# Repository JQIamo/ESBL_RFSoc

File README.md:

# ESBL_RFSoc

Pure sinusoidal phase modulator for electronic sideband locking (ESB locking/ESBL) based on the [RFSoC 4x2](https://www.realdigital.org/hardware/rfsoc-4x2) platform.

## Table of Contents

- [Overview](#overview)
- [Project Structure](#project-structure)
- [System Architecture](#system-architecture)
- [Operation Theory](#operation-theory)
- [Paper and Contact](#paper-and-contact)

## Overview

This repository contains the hardware and software for an RFSoC-based direct SDR that generates the phase-modulated radio-frequency (rf) drive used in electronic sideband Pound–Drever–Hall (PDH) laser locking. The design runs on the AMD Zynq UltraScale+ RFSoC ZU48DR on the [RFSoC 4x2](https://www.realdigital.org/hardware/rfsoc-4x2) platform. It synthesizes the required in-phase and quadrature-phase (I/Q) baseband waveforms in the programmable logic (PL), then uses the on-chip RF Data Converter (RFDC) and RF digital-to-analog converter (RF-DAC) to produce the analog output for an electro-optic modulator (EOM).

The repository includes the FPGA gateware and its Migen source, the PYNQ-side control server and startup scripts, and host-side integration with labscript/BLACS. It also contains the KiCad design for an RFSoC adapter board, simulation testbenches, and Jupyter notebooks for hardware tests. The interface software controls the modulation frequency and depth, I/Q amplitudes and relative phase, PDH reference phase, DAC carrier frequency and output level, and programmed carrier-frequency ramps.

## Project Structure

The main directories and their roles are:

```text
.
├── PYNQ_interface/
│   ├── parser.py
│   ├── ESBL_autostart.sh
│   ├── ESBL_service_enable.sh
│   └── ESBL_startup.service
├── gateware/
│   ├── hdl/
│   ├── python/
│   ├── scripts/
│   ├── sim/
│   └── makefile
├── kicad/
│   └── esb_rfsoc_adapter/
├── labscript_devices/
│   └── ESBL_RFSoC/
└── notebooks/
```

- **`PYNQ_interface/`** — Runtime software for the RFSoC processing system (PS). `parser.py` loads the FPGA overlay, configures the RFDC and memory-mapped control registers, and runs the TCP/IP command server. The shell scripts and systemd unit install and launch the server automatically at boot. The accompanying directory README describes deployment on the board.

- **`gateware/hdl/`** — Verilog RTL used by the Vivado design. The main modules implement the phase-modulated I/Q waveform generator, AXI-Lite control registers, the DMA-driven RFDC NCO frequency-update controller, trigger logic, and the serialized reference output. The `.init` files provide lookup-table initialization data used by the waveform generator. The directory also includes the board-level top-level and wrapper HDL files.

- **`gateware/python/`** — Migen source used to generate the phase-generator Verilog. `esbl_parallel_with_PDH.py` generates the parallel phase-modulator implementation used by the design; `esbl_with_PDH_out_hi_res.py` and `small_test.py` provide alternate or reduced test implementations. The `compile` helper runs the generator and places the generated RTL and lookup-table files in the HDL tree.

- **`gateware/scripts/`** — Vivado Tcl project and block-design setup, plus a helper script for downloading the RFSoC 4x2 board-support files and PMOD constraints required by the build.

- **`gateware/sim/`** — Verilog/SystemVerilog testbenches for the phase generator and the DMA-based frequency-update controller, together with simulation waveform configuration.

- **`gateware/makefile`** — Convenience targets for downloading board files, building the Vivado design, deploying the generated bitstream and hardware-handoff file to the RFSoC, and cleaning Vivado logs.

- **`kicad/`** — KiCad schematic, PCB layout, project settings, and custom footprint for the `esb_rfsoc_adapter` board.

- **`labscript_devices/ESBL_RFSoC/`** — labscript device definition and registration, BLACS worker and tab implementation, and the Qt UI used to control the RFSoC from a labscript/BLACS experiment setup.

- **`notebooks/`** — Jupyter notebooks for manually loading and exercising the overlay and for testing the TCP/IP command interface.

## System Architecture

The instrument is organized into a host-control path and a real-time signal-generation path. The host PC communicates with a PYNQ application running on the RFSoC PS. The PYNQ server loads the FPGA overlay, accesses the hardware through the RFSoC Python APIs and memory-mapped registers, and translates the requested waveform settings into register writes or RFDC configuration updates. The server listens for TCP/IP commands; the BLACS worker uses the same connection to send settings and frequency-ramp instructions.

The PL contains the baseband waveform generator and the control logic. The AXI-Lite register block supplies the generator with the baseband modulation-frequency word, modulation-depth scaling, relative I/Q phase, I- and Q-channel amplitude settings, and PDH reference phase. The software trigger flag is also exposed through this register interface. The phase generator uses a phase accumulator and sine/cosine lookup-and-interpolation logic to calculate the I/Q samples. These samples are packed into an AXI-Stream word and sent to the RFDC. In parallel, the generator produces an eight-bit, phase-adjustable reference waveform; a serializer transfers this signal to a PMOD output.

The RFDC performs digital up-conversion: its NCO supplies the tunable carrier, and its interpolation and signal-conditioning stages prepare the waveform for conversion by the RF-DAC. The resulting analog rf signal is amplified as required and applied to the EOM. The DAC sampling-clock network uses the RFSoC clocking hardware, including the LMK04828 jitter-cleaner circuitry, to provide the clocks required by the data converter and to limit clock-jitter contributions.

Carrier-frequency ramps use a separate DMA path. The PYNQ server converts a requested sequence of carrier frequencies into RFDC frequency-tuning words (FTWs), stores the words in a DMA buffer, and transfers them through AXI DMA to the custom `frequency_change_DMA` controller. That controller issues NCO update requests and advances through the programmed sequence when its trigger condition is met. The trigger logic combines the external PMOD trigger input with the software trigger flag, allowing a ramp to be advanced from software or synchronized to an external experiment trigger. This separates fast carrier updates from the slower host command path.

## Operation Theory

### ESB locking

In ESB locking, the EOM is driven by a phase-modulated rf waveform of the form

$$V_{\mathrm{EOM}}(t)=\xi\sin\left[\Omega_c t+\beta_m\sin(\Omega_m t)\right],$$

where $\Omega_c$ is the tunable rf carrier frequency, $\Omega_m$ is the baseband phase-modulation frequency used for PDH demodulation, and $\beta_m$ is the phase-modulation index. The optical field after phase modulation can be written as

$$E(t)=E_0\exp\left(j\Omega_0t+j\beta_c\sin\left[\Omega_ct+\beta_m\sin(\Omega_mt)\right]\right),$$

where $\Omega_0$ is the unmodulated laser frequency and $\beta_c$ is the optical phase-modulation depth set by the rf drive amplitude. Expanding the field with the Jacobi–Anger identity gives optical components at frequencies $\Omega_0+n\Omega_c+k\Omega_m$, with amplitudes proportional to $J_n(\beta_c)J_k(n\beta_m)$.

The cavity is locked to one of the first-order carrier sidebands, so the lock condition is

$$
\Omega_0\pm\Omega_c=2\pi N\,\mathrm{FSR},
$$

where $N$ is the cavity longitudinal-mode index and FSR is its free spectral range. Once the selected cavity mode is fixed, changing $\Omega_c$ shifts the locked laser carrier frequency by the opposite amount. This is the basis of continuous laser-frequency tuning while retaining the cavity reference. The PDH error signal is obtained by demodulating the detected signal at $\Omega_m$; the relevant signal components form a triplet around the cavity-resonant sideband.

### QAM synthesis of the ESB waveform

The required waveform can be generated by quadrature amplitude modulation (QAM). Applying the angle-sum identity gives

$$
\begin{aligned}
V_{\mathrm{EOM}}(t)
&=\xi\sin\left[\Omega_ct+\beta_m\sin(\Omega_mt)\right]\\
&=I(t)\cos(\Omega_ct)+Q(t)\sin(\Omega_ct),
\end{aligned}
$$

with the ideal baseband components

$$
\begin{aligned}
I(t)&=\xi\sin\left[\beta_m\sin(\Omega_mt)\right],\\
Q(t)&=\xi\cos\left[\beta_m\sin(\Omega_mt)\right].
\end{aligned}
$$

Thus, two carrier components separated by $\pi/2$ are independently amplitude-modulated by $I(t)$ and $Q(t)$ and then summed. For an ideal waveform, $I(t)^2+Q(t)^2=\xi^2$ is constant, while the I/Q phasor angle follows the desired sinusoidal phase modulation. This produces a constant-envelope phase-modulated rf signal rather than relying on a small-index approximation.

In this implementation, the PL generates the baseband I/Q samples digitally. A phase accumulator establishes the $\Omega_m$ timebase, and sine/cosine lookup and interpolation logic generates the modulation functions. The modulation-depth setting scales the phase excursion; the I/Q amplitude and relative-phase settings provide adjustment of the generated phasor. The RFDC NCO then supplies $\Omega_c$ and up-converts the I/Q stream to the output carrier frequency. The PYNQ/PL is also capable of directly adjusting the I/Q impairment calibrations.

## Paper and Contact

Please refer to the [preprint](https://arxiv.org/abs/2409.08764) for details about the theoretical analysis, waveform characterization, and experimental application of this device.

Please contact Alessandro Restelli (arestell"at"umd"dot"edu) or Juntian Tu (juntian"at"umd"dot"edu) for issues related to this repository.

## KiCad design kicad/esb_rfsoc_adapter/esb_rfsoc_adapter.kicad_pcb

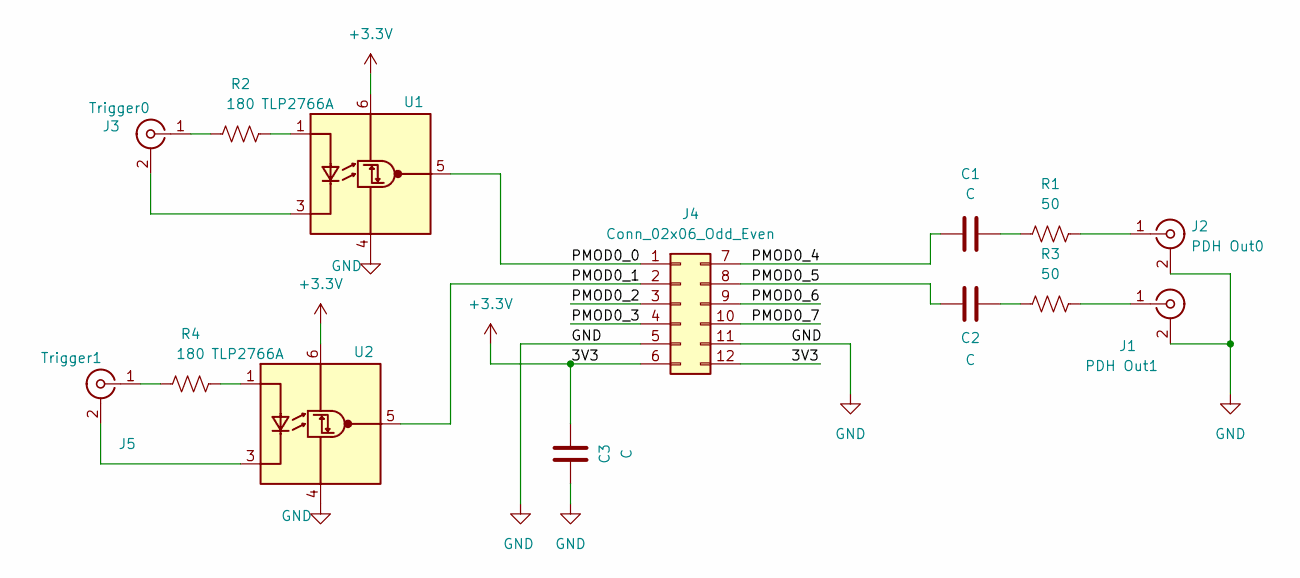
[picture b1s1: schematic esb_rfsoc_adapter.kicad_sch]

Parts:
C1, C2, C3: C; C_0603_1608Metric
J1: PDH Out1; SMA_Amphenol_901-144_Vertical
J2: PDH Out0; SMA_Amphenol_901-144_Vertical
J3: Trigger0; SMA_Amphenol_901-144_Vertical
J4: Conn_02x06_Odd_Even; pinheader_2x6
J5: Trigger1; SMA_Amphenol_901-144_Vertical
R1, R3: 50; R_0603_1608Metric
R2, R4: 180; R_0603_1608Metric
U1, U2: TLP2766A; SO-6L_10x3.84mm_P1.27mm

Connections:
+3.3V: C3.2, J4.6, J4.12, U1.6 (VDD), U2.6 (VDD)
/PMOD0_0: J4.1, U1.5 (VO)
/PMOD0_1: J4.2, U2.5 (VO)
/PMOD0_2: J4.3
/PMOD0_3: J4.4
/PMOD0_4: C1.1, J4.7
/PMOD0_5: C2.1, J4.8
/PMOD0_6: J4.9
/PMOD0_7: J4.10
GND: C3.1, J1.2 (Ext), J2.2 (Ext), J4.5, J4.11, U1.4 (GND), U2.4 (GND)
unnamed: C1.2, R1.1
unnamed: C2.2, R3.1
unnamed: J1.1 (In), R3.2
unnamed: J2.1 (In), R1.2
unnamed: J3.2 (Ext), U1.3 (K)
unnamed: J3.1 (In), R2.1
unnamed: J5.2 (Ext), U2.3 (K)
unnamed: J5.1 (In), R4.1
unnamed: R2.2, U1.1 (A)
unnamed: R4.2, U2.1 (A)

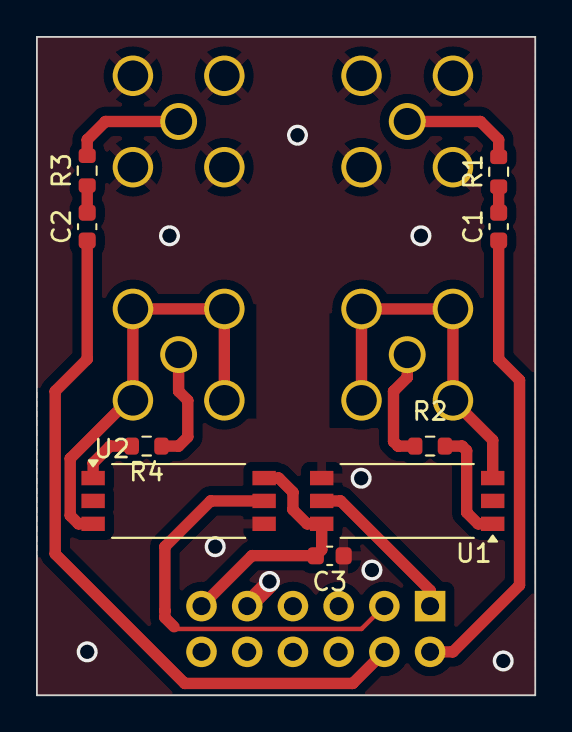
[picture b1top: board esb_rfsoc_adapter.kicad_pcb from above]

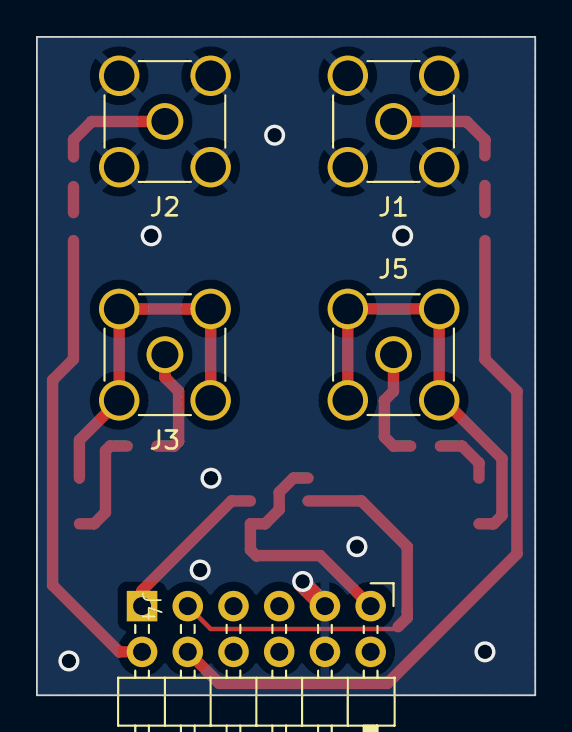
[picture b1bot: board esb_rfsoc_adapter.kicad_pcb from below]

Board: 2 copper layers, 27.7 x 36.6 mm, 14 parts (5 on the bottom side), 16 nets.

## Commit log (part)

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2024-12-12 Code written so far added
    It should be possibile to recreate the Vivado project with "make build"
    In "notebooks" there is a copy of the notebook that needs to be copyed in the evaluation board folder
    The project is currently not outputing any signal --> debug needed
2024-12-12 temporarely saved phase_generator but needs to figure out how to specify folder for lut.init
2024-12-12 added the MMIO line in the notebook
2024-12-13 First fully working design Yeeeea!
    caveat: before synthesizing it is still needed to change the part of lut*.init files to absolute
    We need to find a solution.
    TO DO:
    1) Figuring out reference outputs and trigger(s) (PMOD)
    2) Doubling the system so that 2 channels are possibile
    3) Intercepting AXI or writing C code to allow for external configurations
2024-12-19 DMA and direct register writing
    1) Added a DMA engine that needs debug
    2) Added memory allocation in notebook
    2) Added MMIO direct mapping of XRFDC in notebook
2024-12-29 1) Fixed the TCL script from main branch so that it could be compiled successfully (there is still unconnected pins left); 2) Modified the Jupyter notebook so that to set the rfdc EventSource correct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
2025-01-03 Add an on-board python server compatible for labscript remote interface
2025-01-08 Tested parser.py; added labscript device implementation
2025-01-14 Script updated with DMA
2025-01-14 Added adapter board design; added a tester client
2025-01-15 Fixed and tested the triggered DMA functionality.
2025-01-16 On-board parser server and labscript interface updated to cooperate with the new triggering function and clock settings.
2025-01-22 Python implememtation with full NCO in Migen at max frequency rate
2025-01-23 1) Add the auto start service at the bootup process; 2) Adjusted the phase generator code so it only reads from 2 look-up tables
2025-01-29 1) Tested and debugged the labscript interface; 2) added a function to save and load the modulation configurations which will be loaded at the program startup
2025-01-31 Fixed bug in "PM" command after testing with a real PDH laser lock
2025-03-21 estimation of lsb error
2025-03-21 Added the capability of adding an offset to I and Q
    The python method add_offsets(I,Q) in the ESBL notebook can be used to adjust these values
    Make sure to leave enough headroom in the I and Q gain to accomodate offsets.
    Example: Gain = 0x00007FFF and offset = 0x00003FFF (offset is 16 bit 2s complement while the gain is 16 bit unsigned so 3FFF maps to half of the available range)
2025-03-24 Code cleanup after an unsusccessful synthesis
    1) Migen code was regenerated after we found out that the phase control for the PDH signal was not responsive
    2) Since I was at it I finally solved the issue with the relative path for the *.init files
    SOLUTION: It turns out they must be added to the project and they need to have a *.mem extension
    Changes to be committed:
    new file: hdl/lut/lut.mem
    new file: hdl/lut/lut_1.mem
2025-03-24 Code cleanup
    1) No nead to specify absolute path for memory configuration files
2025-03-24 found alternative to unsupported <dir> command in TCL script glob is the key!
2025-03-24 Substituted unsupported <dir> with <glob> in TCL file
2025-03-24 Fixed rebasing gone wrong
    I forgot to save the file before rebasing with the result of having the patch notation still in the file.
2025-03-27 Added a migen testbench for the I_Q_generator
